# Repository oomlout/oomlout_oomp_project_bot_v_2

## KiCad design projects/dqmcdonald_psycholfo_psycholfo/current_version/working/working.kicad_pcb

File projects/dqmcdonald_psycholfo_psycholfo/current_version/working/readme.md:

# psycholfo
 
## summary 
* id: dqmcdonald_psycholfo_psycholfo
* user: dqmcdonald
* name: psycholfo
* board: psycholfo
* repo: https://github.com/dqmcdonald/PsychoLFO
* src_file_repo_kicad_pcb: PsychoLFO.kicad_pcb
* src_file_repo_kicad_pcb_link: https://github.com/dqmcdonald/PsychoLFO/tree/master/PsychoLFO.kicad_pcb

* src_file_repo_sch: PsychoLFO.sch
* src_file_repo_sch_link: https://github.com/dqmcdonald/PsychoLFO/tree/master/PsychoLFO.sch
* full details link: https://github.com/oomlout/oomlout_oomp_project_bot_v_2/tree/main/projects/dqmcdonald_psycholfo_psycholfo/current_version/working

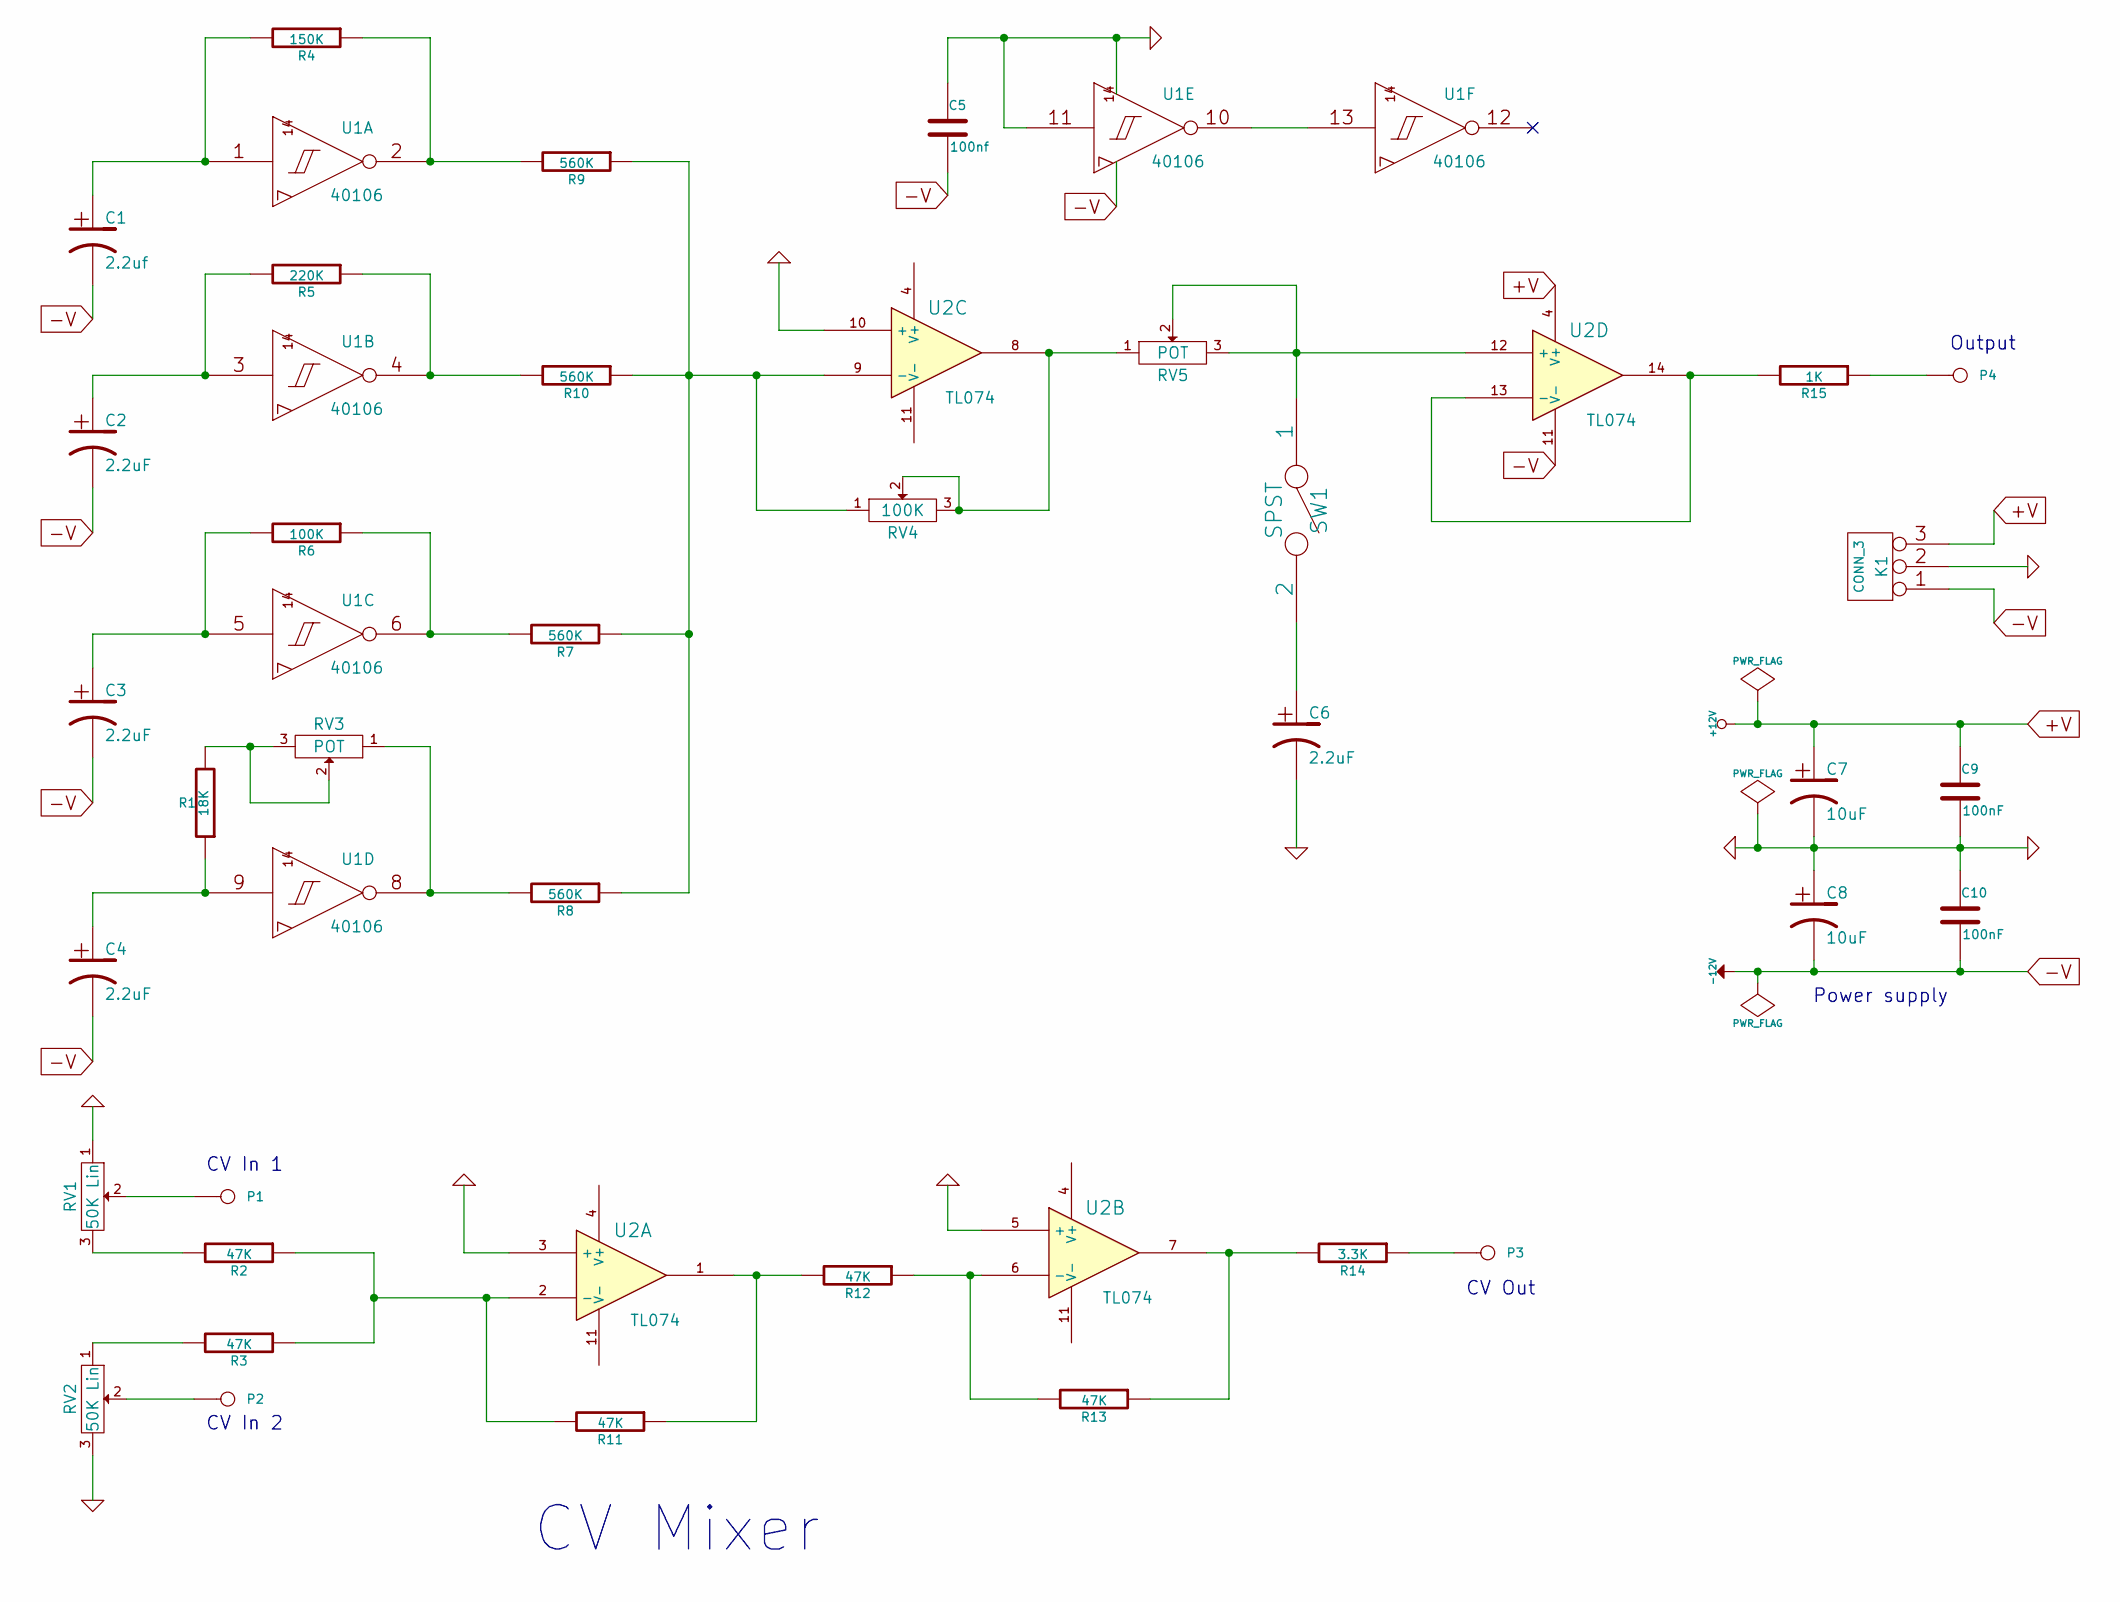
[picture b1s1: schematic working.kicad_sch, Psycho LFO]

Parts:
C1: 2.2uf
C2, C3, C4, C6: 2.2uF
C5: 100nf
C7, C8: 10uF
C9, C10: 100nF
K1: CONN_3
P1, P2, P3: CONN_1
P4: Out
R1: 18K
R2, R3, R11, R12, R13: 47K
R4: 150K
R5: 220K
R6: 100K
R7, R8, R9, R10: 560K
R14: 3.3K
R15: 1K
RV1, RV2: 50K Lin
RV3, RV5: POT
RV4: 100K
SW1: SPST
U1: 40106
U2: TL074

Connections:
+V: C7.1, C9.1, K1.3, U2.4 (V+)
-V: C1.2, C2.2, C3.2, C4.2, C5.2, C8.2, C10.2, K1.1, U1.7 (VSS), U2.11 (V-)
GND: C5.1, C6.2, C7.2, C8.1, C9.2, C10.1, K1.2 (PM), RV1.1, RV2.3, U1.11 (In), U1.14 (VDD), U2.3 (+), U2.5 (+), U2.10 (+)
unnamed: C1.1, R4.2, U1.1 (In)
unnamed: C2.1, R5.2, U1.3 (In)
unnamed: C3.1, R6.2, U1.5 (In)
unnamed: C4.1, R1.1, U1.9 (In)
unnamed: C6.1, SW1.2
unnamed: P1.1, RV1.2
unnamed: P2.1, RV2.2
unnamed: P3.1, R14.1
unnamed: P4.1, R15.1
unnamed: R1.2, RV3.2, RV3.3
unnamed: R2.2, RV1.3
unnamed: R3.2, RV2.1
unnamed: R4.1, R9.2, U1.2 (Out)
unnamed: R6.1, R7.2, U1.6 (Out)
unnamed: R8.2, RV3.1, U1.8 (Out)
unnamed: R7.1, R8.1, R9.1, R10.1, RV4.1, U2.9 (-)
unnamed: R5.1, R10.2, U1.4 (Out)
unnamed: R11.1, R12.2, U2.1
unnamed: R2.1, R3.1, R11.2, U2.2 (-)
unnamed: R12.1, R13.2, U2.6 (-)
unnamed: R13.1, R14.2, U2.7
unnamed: R15.2, U2.13 (-), U2.14
unnamed: RV4.2, RV4.3, RV5.1, U2.8
unnamed: RV5.2, RV5.3, SW1.1, U2.12 (+)
unnamed: U1.10 (Out), U1.13 (In)

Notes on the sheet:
CV Out
Power supply
Output
CV Mixer
CV In 1
CV In 2

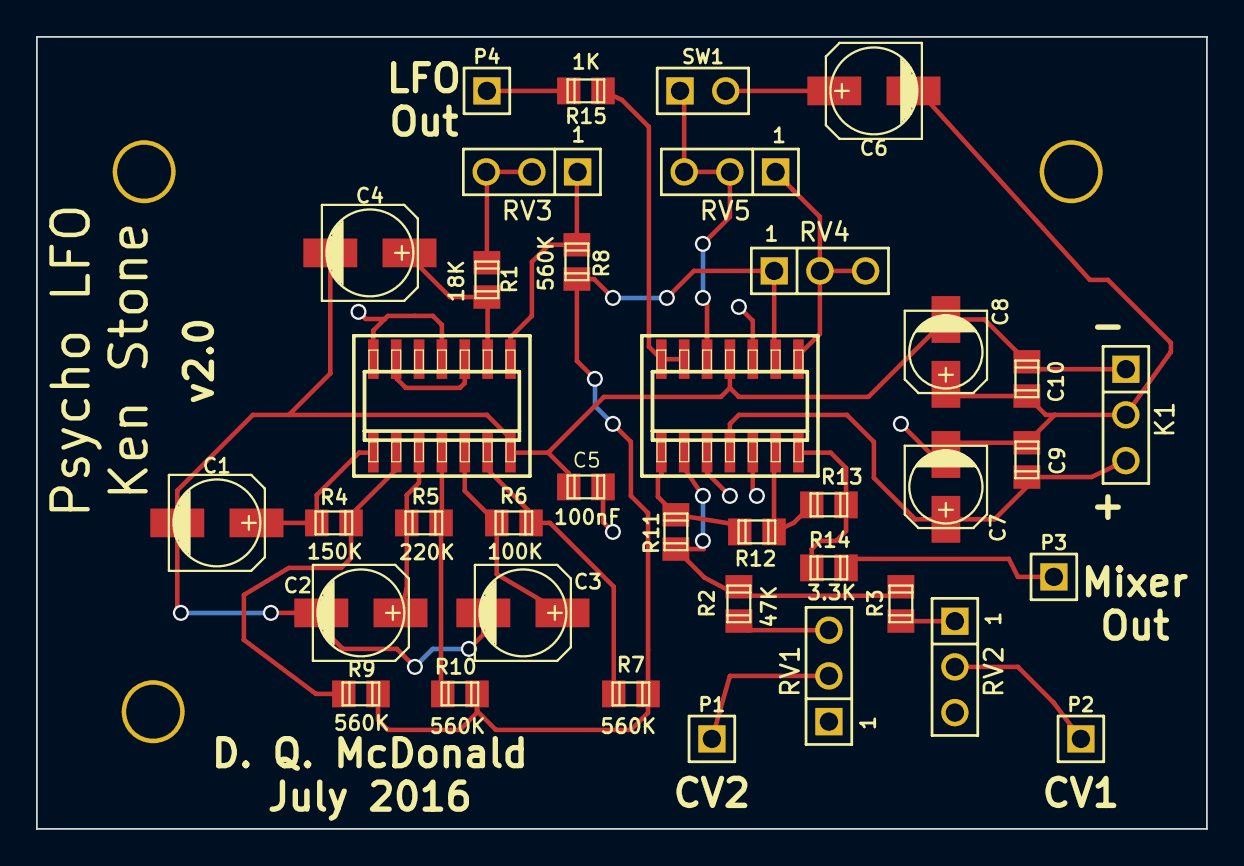
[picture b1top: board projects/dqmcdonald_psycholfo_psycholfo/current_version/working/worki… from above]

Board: 2 copper layers, 65.0 x 44.0 mm, 38 parts (0 on the bottom side), 28 nets.

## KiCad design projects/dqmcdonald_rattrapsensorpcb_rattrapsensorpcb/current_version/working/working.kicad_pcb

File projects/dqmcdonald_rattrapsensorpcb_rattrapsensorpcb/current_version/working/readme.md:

# rattrapsensorpcb
 
## summary 
* id: dqmcdonald_rattrapsensorpcb_rattrapsensorpcb
* user: dqmcdonald
* name: rattrapsensorpcb
* board: rattrapsensorpcb
* repo: https://github.com/dqmcdonald/RatTrapSensorPCB
* src_file_repo_kicad_pcb: RatTrapSensorPCB.kicad_pcb
* src_file_repo_kicad_pcb_link: https://github.com/dqmcdonald/RatTrapSensorPCB/tree/master/RatTrapSensorPCB.kicad_pcb

* src_file_repo_sch: RatTrapSensorPCB.sch
* src_file_repo_sch_link: https://github.com/dqmcdonald/RatTrapSensorPCB/tree/master/RatTrapSensorPCB.sch
* full details link: https://github.com/oomlout/oomlout_oomp_project_bot_v_2/tree/main/projects/dqmcdonald_rattrapsensorpcb_rattrapsensorpcb/current_version/working

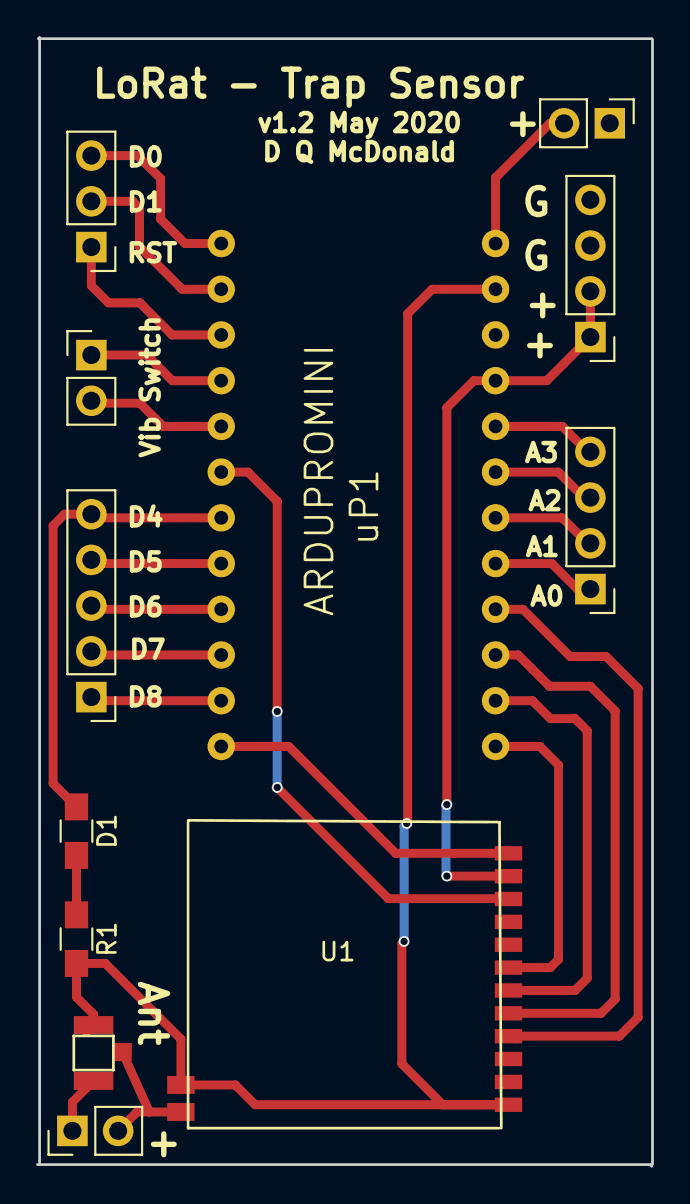
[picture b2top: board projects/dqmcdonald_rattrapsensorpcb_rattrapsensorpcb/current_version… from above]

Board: 2 copper layers, 34.2 x 62.7 mm, 4 parts (0 on the bottom side), 10 nets.

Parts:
D1: LED; R_0805_HandSoldering
R1: 220; R_0805_HandSoldering
U1: LoRaSx1276
uP1: ARDUPROMINI; ArduProMini

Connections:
D3: U1.10, uP1.12
D4: D1.1, uP1.13
D9: U1.12, uP1.18
GND: R1.2, U1.1, U1.14, uP1.10, uP1.20
MISO: U1.5, uP1.28
MOSI: U1.6, uP1.29
NSS: U1.7, uP1.30
unnamed: D1.2, R1.1
SCK: U1.4, uP1.27
V3.3: U1.11, uP1.22

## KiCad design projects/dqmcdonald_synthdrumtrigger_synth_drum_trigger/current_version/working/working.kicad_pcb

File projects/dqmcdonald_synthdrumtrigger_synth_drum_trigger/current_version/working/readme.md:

# synthdrumtrigger
 
## summary 
* id: dqmcdonald_synthdrumtrigger_synth_drum_trigger
* user: dqmcdonald
* name: synthdrumtrigger
* board: synth_drum_trigger
* repo: https://github.com/dqmcdonald/SynthDrumTrigger
* src_file_repo_kicad_pcb: Synth Drum Trigger.kicad_pcb
* src_file_repo_kicad_pcb_link: https://github.com/dqmcdonald/SynthDrumTrigger/tree/master/Synth Drum Trigger.kicad_pcb

* src_file_repo_sch: Synth Drum Trigger.sch
* src_file_repo_sch_link: https://github.com/dqmcdonald/SynthDrumTrigger/tree/master/Synth Drum Trigger.sch
* full details link: https://github.com/oomlout/oomlout_oomp_project_bot_v_2/tree/main/projects/dqmcdonald_synthdrumtrigger_synth_drum_trigger/current_version/working

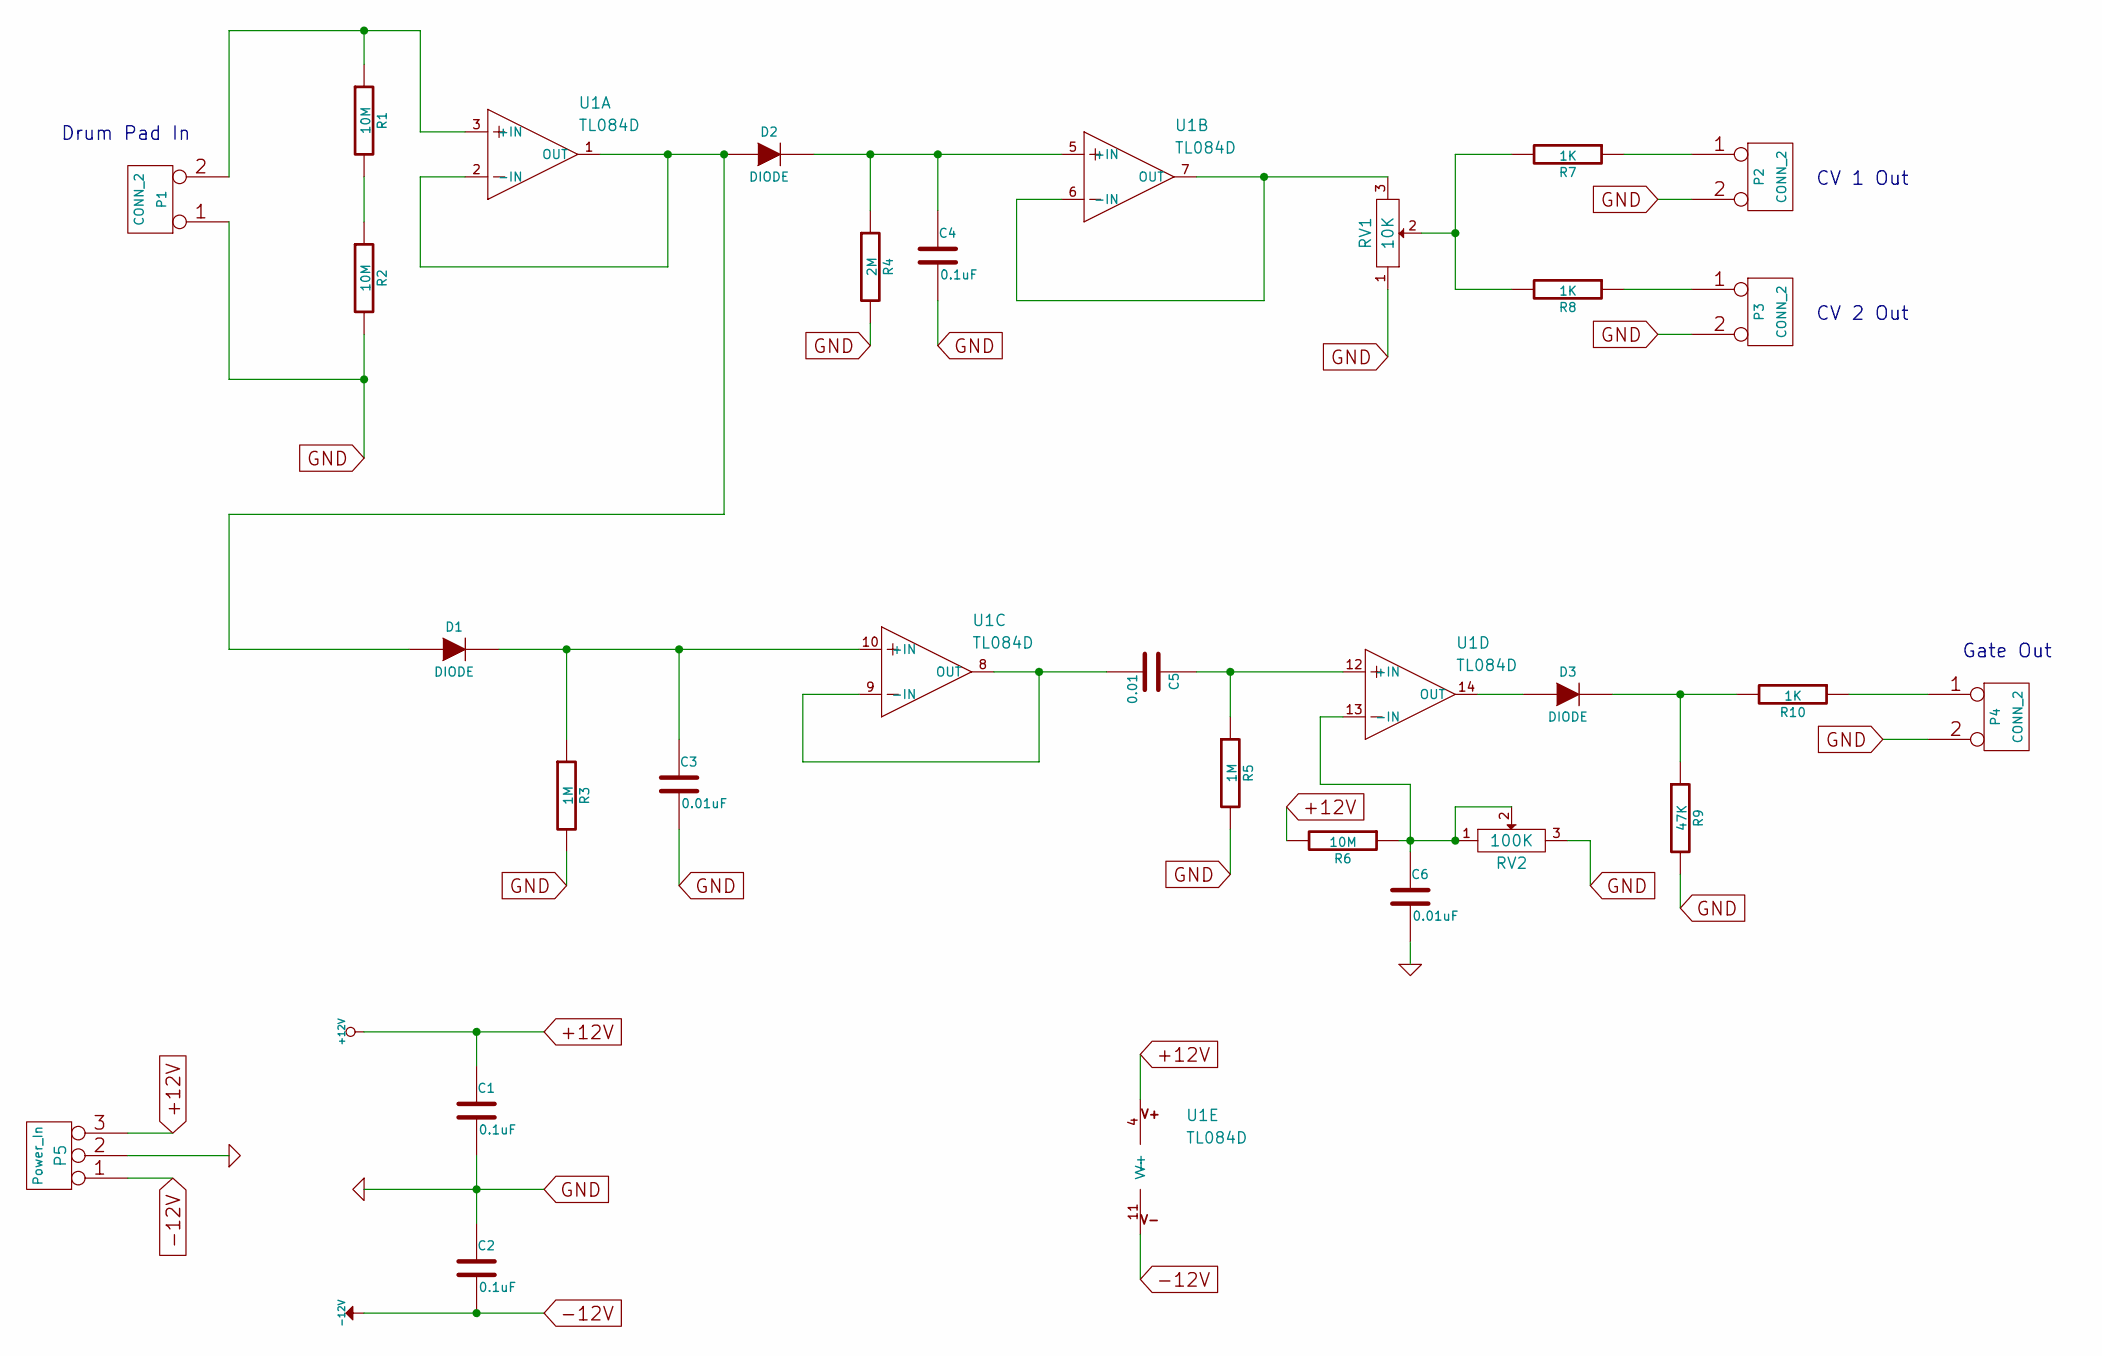
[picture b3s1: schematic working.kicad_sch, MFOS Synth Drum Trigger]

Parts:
C1, C2, C4: 0.1uF
C3, C6: 0.01uF
C5: 0.01
D1, D2, D3: DIODE
P1, P2, P3, P4: CONN_2
P5: Power_In
R1, R2, R6: 10M
R3, R5: 1M
R4: 2M
R7, R8, R10: 1K
R9: 47K
RV1: 10K
RV2: 100K
U1: TL084D; op-amp-SO14

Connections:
+12V: C1.1, P5.3 (+12V), R6.2, U1.4 (V+)
-12V: C2.2, P5.1 (-12V), U1.11 (V-)
GND: C1.2, C2.1, C3.2, C4.2, C6.2, P1.1 (VCC), P2.2 (GND), P3.2 (GND), P4.2 (GND), P5.2 (Gnd), R2.2, R3.2, R4.2, R5.2, R9.2, RV1.1, RV2.3
unnamed: C3.1, D1.2 (K), R3.1, U1.10 (+IN)
unnamed: C4.1, D2.2 (K), R4.1, U1.5 (+IN)
unnamed: C5.1, R5.1, U1.12 (+IN)
unnamed: C5.2, U1.8 (OUT), U1.9 (-IN)
unnamed: C6.1, R6.1, RV2.1, RV2.2, U1.13 (-IN)
unnamed: D1.1 (A), D2.1 (A), U1.1 (OUT), U1.2 (-IN)
unnamed: D3.1 (A), U1.14 (OUT)
unnamed: D3.2 (K), R9.1, R10.2
unnamed: P1.2 (GND), R1.1, U1.3 (+IN)
unnamed: P2.1 (VCC), R7.1
unnamed: P3.1 (VCC), R8.1
unnamed: P4.1 (VCC), R10.1
unnamed: R1.2, R2.1
unnamed: R7.2, R8.2, RV1.2
unnamed: RV1.3, U1.6 (-IN), U1.7 (OUT)

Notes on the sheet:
CV 2 Out
CV 1 Out
Gate Out
Drum Pad In

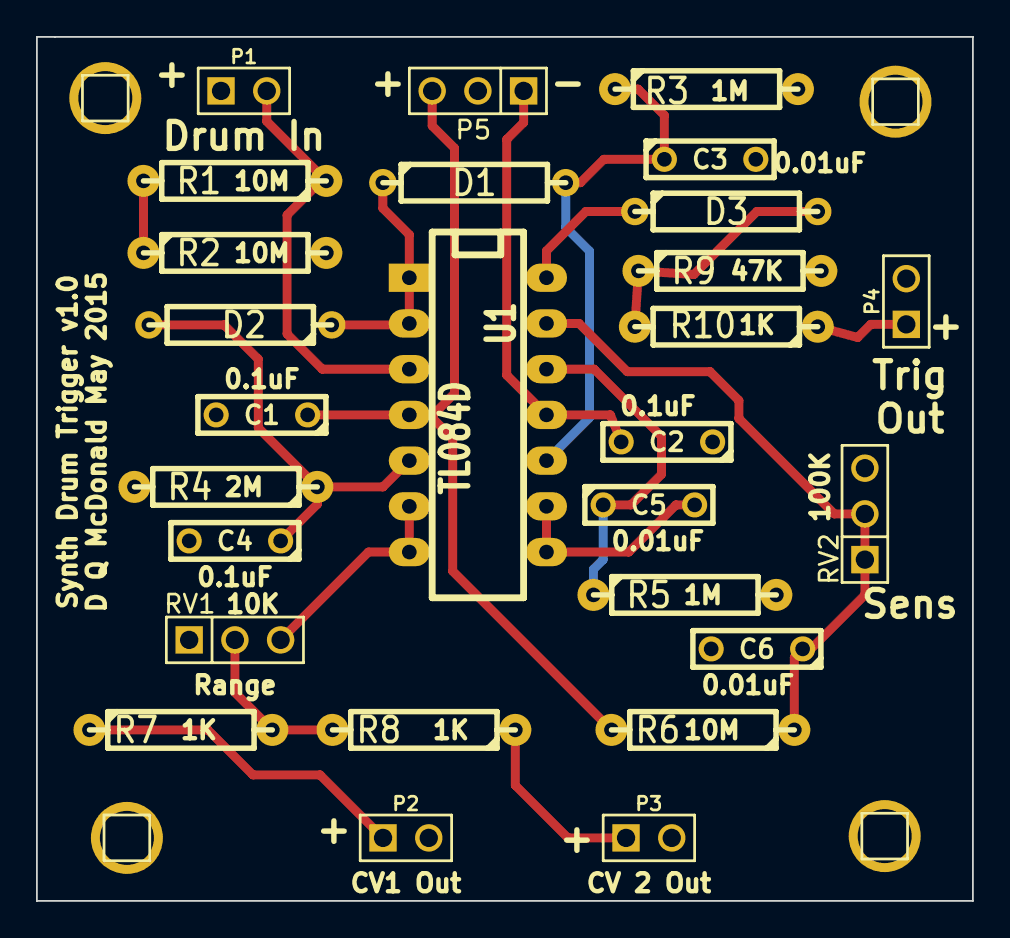
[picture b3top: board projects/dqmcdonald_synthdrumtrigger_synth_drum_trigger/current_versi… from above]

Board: 2 copper layers, 52.0 x 48.0 mm, 27 parts (0 on the bottom side), 18 nets.

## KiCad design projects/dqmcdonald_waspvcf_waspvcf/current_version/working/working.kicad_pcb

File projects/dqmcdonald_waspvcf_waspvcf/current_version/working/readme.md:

# waspvcf
 
## summary 
* id: dqmcdonald_waspvcf_waspvcf
* user: dqmcdonald
* name: waspvcf
* board: waspvcf
* repo: https://github.com/dqmcdonald/WaspVCF
* src_file_repo_kicad_pcb: WaspVCF.kicad_pcb
* src_file_repo_kicad_pcb_link: https://github.com/dqmcdonald/WaspVCF/tree/master/WaspVCF.kicad_pcb

* src_file_repo_sch: WaspVCF.sch
* src_file_repo_sch_link: https://github.com/dqmcdonald/WaspVCF/tree/master/WaspVCF.sch
* full details link: https://github.com/oomlout/oomlout_oomp_project_bot_v_2/tree/main/projects/dqmcdonald_waspvcf_waspvcf/current_version/working

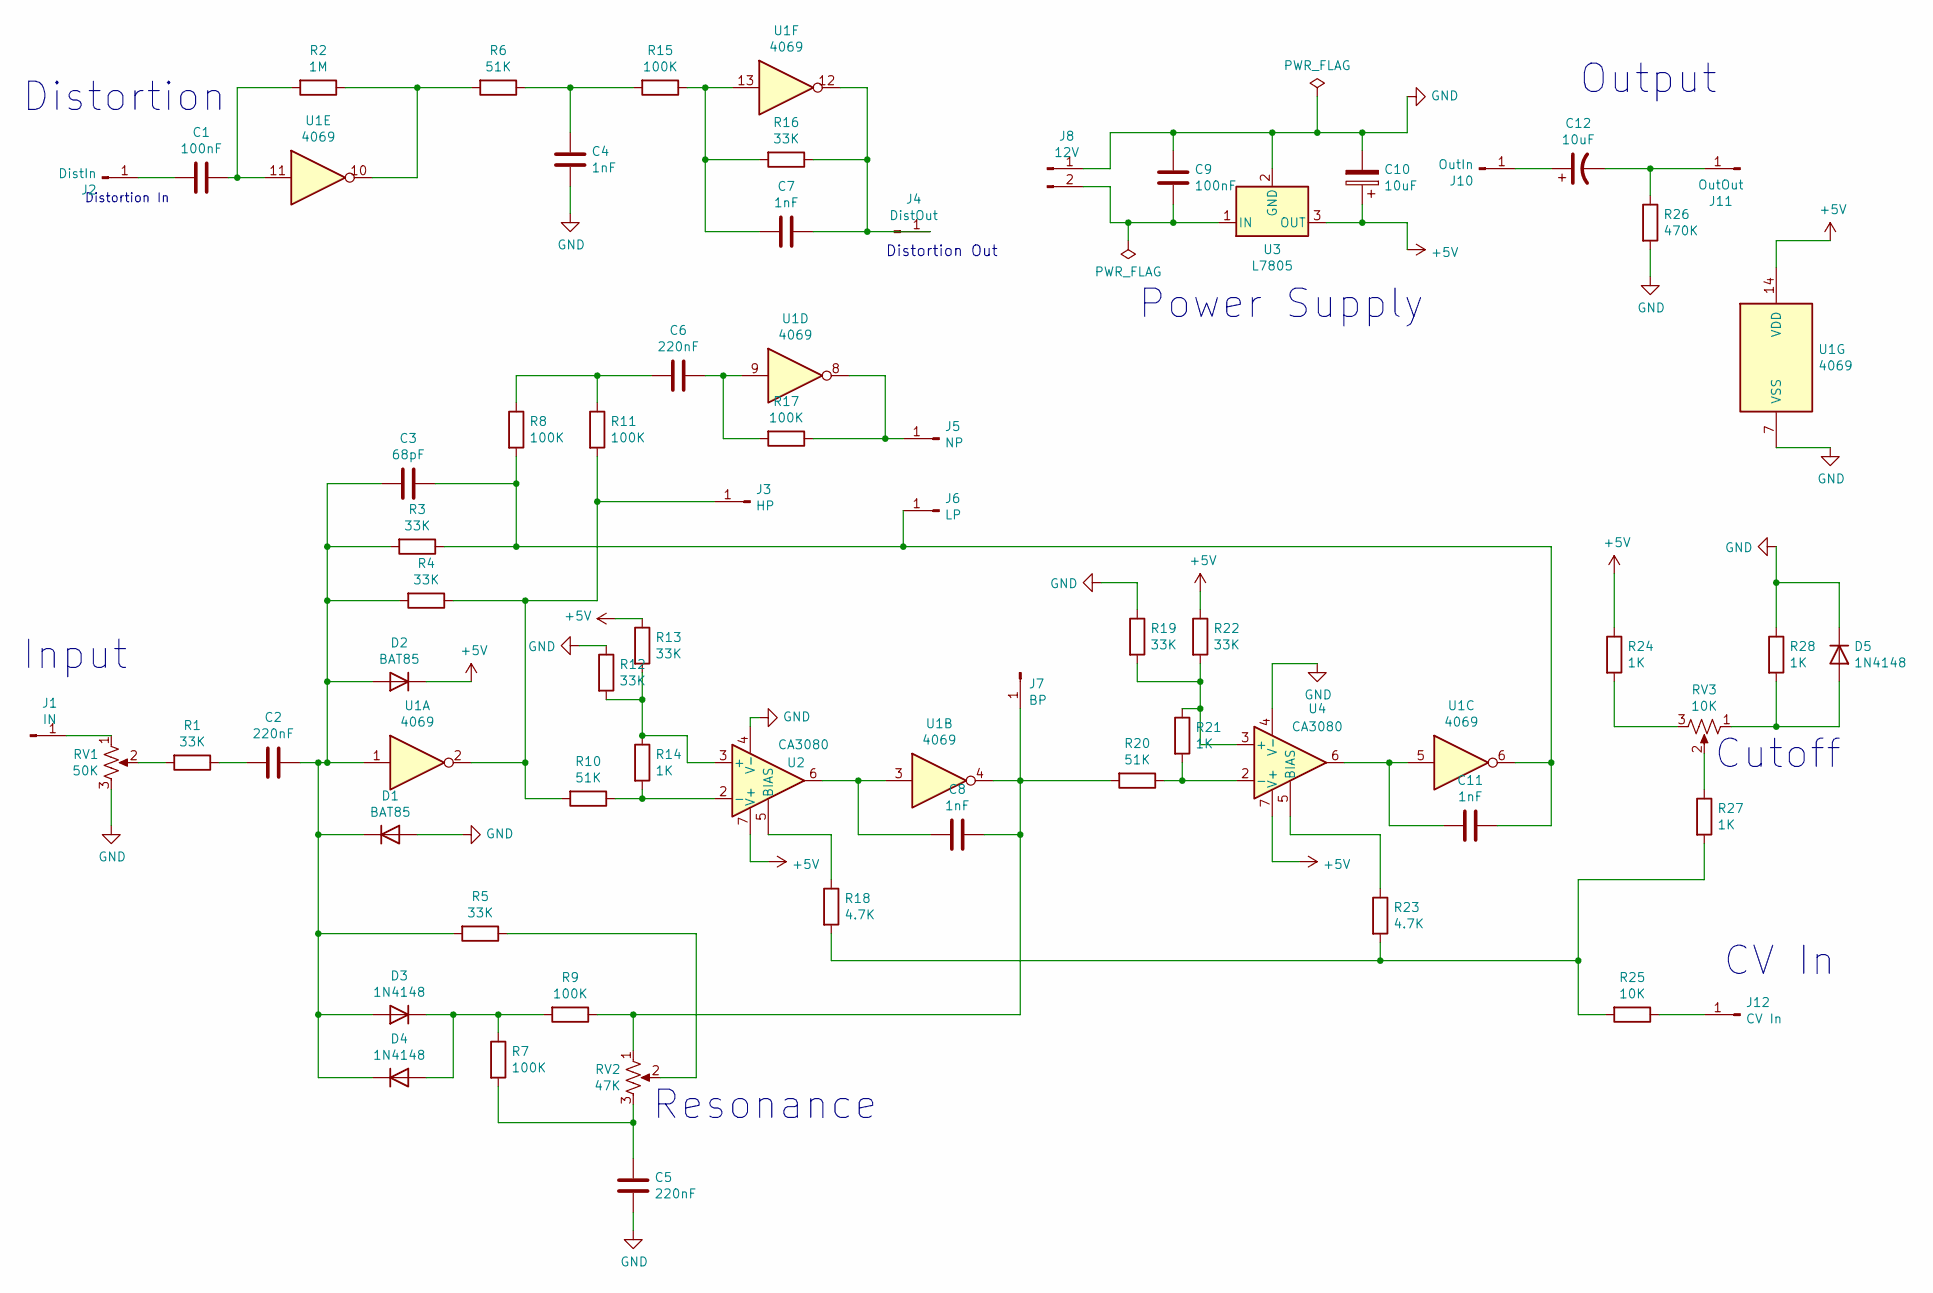
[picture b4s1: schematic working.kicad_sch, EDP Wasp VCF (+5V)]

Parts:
C1, C9: 100nF; C_Disc_D6.0mm_W2.5mm_P5.00mm
C2, C5, C6: 220nF; C_Disc_D6.0mm_W2.5mm_P5.00mm
C3: 68pF; C_Disc_D6.0mm_W2.5mm_P5.00mm
C4, C7, C8, C11: 1nF; C_Disc_D6.0mm_W2.5mm_P5.00mm
C10, C12: 10uF; CP_Radial_D5.0mm_P2.50mm
D1, D2: BAT85; D_T-1_P5.08mm_Horizontal
D3, D4, D5: 1N4148; D_T-1_P5.08mm_Horizontal
J1: IN; Pin_Header_Straight_1x01_Pitch2.54mm
J2: DistIn; Pin_Header_Straight_1x01_Pitch2.54mm
J3: HP; Pin_Header_Straight_1x01_Pitch2.54mm
J4: DistOut; Pin_Header_Straight_1x01_Pitch2.54mm
J5: NP; Pin_Header_Straight_1x01_Pitch2.54mm
J6: LP; Pin_Header_Straight_1x01_Pitch2.54mm
J7: BP; Pin_Header_Straight_1x01_Pitch2.54mm
J8: 12V; Pin_Header_Straight_1x02_Pitch2.54mm
J10: OutIn; Pin_Header_Straight_1x01_Pitch2.54mm
J11: OutOut; Pin_Header_Straight_1x01_Pitch2.54mm
J12: CV In; Pin_Header_Straight_1x01_Pitch2.54mm
R1, R3, R4, R5, R12, R13, R16, R19, R22: 33K; R_Axial_DIN0207_L6.3mm_D2.5mm_P7.62mm_Horizontal
R2: 1M; R_Axial_DIN0207_L6.3mm_D2.5mm_P7.62mm_Horizontal
R6, R10, R20: 51K; R_Axial_DIN0207_L6.3mm_D2.5mm_P7.62mm_Horizontal
R7, R8, R9, R11, R15, R17: 100K; R_Axial_DIN0207_L6.3mm_D2.5mm_P7.62mm_Horizontal
R14, R21, R24, R27, R28: 1K; R_Axial_DIN0207_L6.3mm_D2.5mm_P7.62mm_Horizontal
R18, R23: 4.7K; R_Axial_DIN0207_L6.3mm_D2.5mm_P7.62mm_Horizontal
R25: 10K; R_Axial_DIN0207_L6.3mm_D2.5mm_P7.62mm_Horizontal
R26: 470K; R_Axial_DIN0207_L6.3mm_D2.5mm_P7.62mm_Horizontal
RV1: 50K; Pin_Header_Straight_1x03_Pitch2.54mm
RV2: 47K; Pin_Header_Straight_1x03_Pitch2.54mm
RV3: 10K; Pin_Header_Straight_1x03_Pitch2.54mm
U1: 4069; DIP-14_W7.62mm_Socket_LongPads
U2: CA3080; DIP-8_W7.62mm_Socket_LongPads
U3: L7805; TO-220-3_Vertical
U4: CA3080; DIP-8_W7.62mm_LongPads

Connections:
+5V: C10.1, D2.1 (K), R13.1, R22.1, R24.1, U1.14 (VDD), U2.7 (V+), U3.3 (OUT), U4.7 (V+)
GND: C4.2, C5.2, C9.1, C10.2, D1.2 (A), D5.1 (K), J8.1, R12.1, R19.1, R26.2, R28.1, RV1.3, U1.7 (VSS), U2.4 (V-), U3.2 (GND), U4.4 (V-)
unnamed: C1.1, R2.2, U1.11
unnamed: C1.2, J2.1
unnamed: C2.1, C3.2, D1.1 (K), D2.2 (A), D3.2 (A), D4.1 (K), R3.2, R4.2, R5.2, U1.1
unnamed: C2.2, R1.1
unnamed: C4.1, R6.1, R15.2
unnamed: C5.1, R7.2, RV2.3
unnamed: C6.1, R17.2, U1.9
unnamed: C6.2, R8.1, R11.1
unnamed: C7.1, J4.1, R16.1, U1.12
unnamed: C7.2, R15.1, R16.2, U1.13
unnamed: C8.1, J7.1, R9.1, R20.2, RV2.1, U1.4
unnamed: C8.2, U1.3, U2.6
unnamed: C9.2, J8.2, U3.1 (IN)
unnamed: C3.1, C11.1, J6.1, R3.1, R8.2, U1.6
unnamed: C11.2, U1.5, U4.6
unnamed: C12.1, J10.1
unnamed: C12.2, J11.1, R26.1
unnamed: D3.1 (K), D4.2 (A), R7.1, R9.2
unnamed: D5.2 (A), R28.2, RV3.1
unnamed: J1.1, RV1.1
unnamed: J3.1, R4.1, R10.2, R11.2, U1.2
unnamed: J5.1, R17.1, U1.8
unnamed: J12.1, R25.1
unnamed: R1.2, RV1.2
unnamed: R2.1, R6.2, U1.10
unnamed: R5.1, RV2.2
unnamed: R10.1, R14.2, U2.2 (-)
unnamed: R12.2, R13.2, R14.1, U2.3 (+)
unnamed: R18.1, U2.5 (BIAS)
unnamed: R18.2, R23.2, R25.2, R27.2
unnamed: R19.2, R21.1, R22.2, U4.3 (+)
unnamed: R20.1, R21.2, U4.2 (-)
unnamed: R23.1, U4.5 (BIAS)
unnamed: R24.2, RV3.3
unnamed: R27.1, RV3.2

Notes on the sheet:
Input
Distortion In
CV In
Distortion Out
Distortion
Cutoff
Resonance
Power Supply
Output

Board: 2 copper layers, 63 parts (0 on the bottom side), 37 nets, no tracks yet.

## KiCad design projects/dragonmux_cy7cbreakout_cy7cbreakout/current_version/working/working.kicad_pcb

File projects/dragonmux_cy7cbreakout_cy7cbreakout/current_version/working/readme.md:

# cy7cbreakout
 
## summary 
* id: dragonmux_cy7cbreakout_cy7cbreakout
* user: dragonmux
* name: cy7cbreakout
* board: cy7cbreakout
* repo: https://github.com/dragonmux/CY7CBreakout
* src_file_repo_kicad_pcb: CY7CBreakout.kicad_pcb
* src_file_repo_kicad_pcb_link: https://github.com/dragonmux/CY7CBreakout/tree/main/CY7CBreakout.kicad_pcb

* src_file_repo_sch: 
* src_file_repo_sch_link: https://github.com/dragonmux/CY7CBreakout/tree/main/
* full details link: https://github.com/oomlout/oomlout_oomp_project_bot_v_2/tree/main/projects/dragonmux_cy7cbreakout_cy7cbreakout/current_version/working

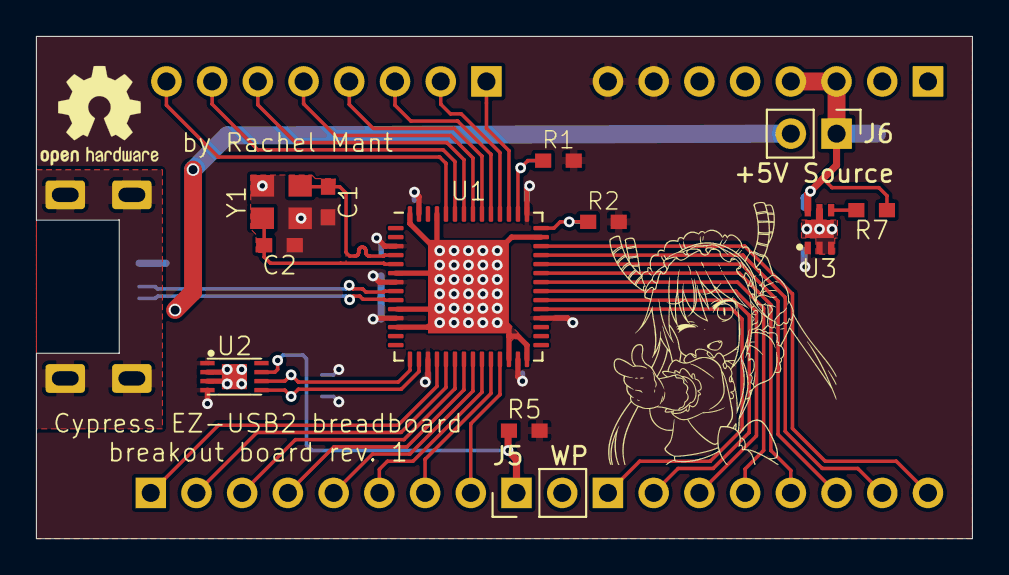
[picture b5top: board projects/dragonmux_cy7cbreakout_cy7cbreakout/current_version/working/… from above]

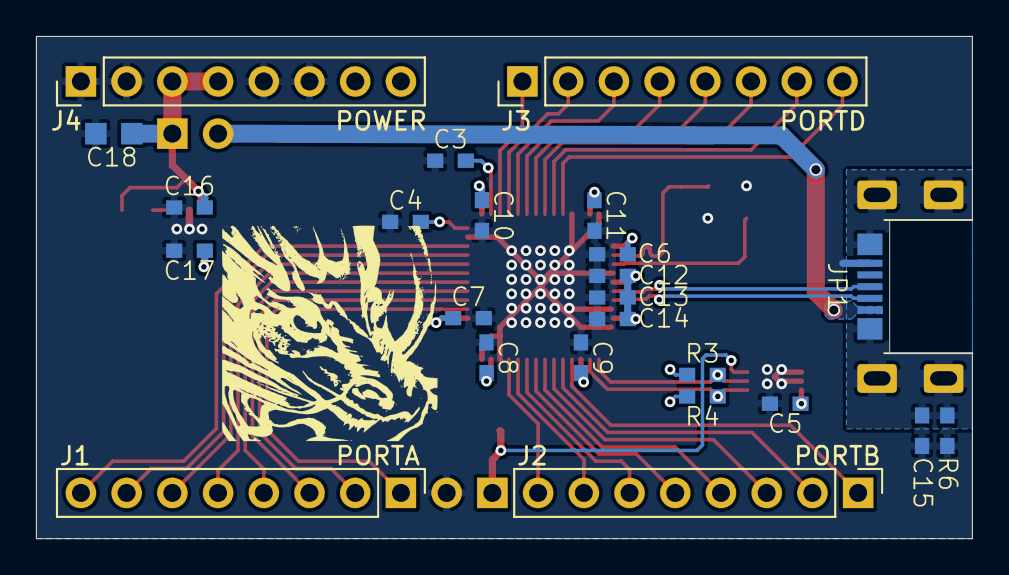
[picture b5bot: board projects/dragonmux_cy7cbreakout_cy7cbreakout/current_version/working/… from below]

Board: 2 copper layers, 52.0 x 27.9 mm, 39 parts (25 on the bottom side), 39 nets.

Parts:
C1, C2: 15pF; C0603
C3, C4: 10uF; C0603
C5, C6, C7, C8, C9, C10, C11, C15: 0.1uF; C0603
C12: 0.22uF; C0603
C13: 10nF; C0603
C14: 1nF; C0603
C16, C17: 4.7uF; C0603
C18: 47uF; C0805
DRG1: トール; トール-12.9x14.8
DRG2: Nagadreth; Nagadreth-12.0x12.0
J1: PORTA; PinHeader_1x08_P2.54mm_Vertical
J2: PORTB; PinHeader_1x08_P2.54mm_Vertical
J3: PORTD; PinHeader_1x08_P2.54mm_Vertical
J4: POWER; PinHeader_1x08_P2.54mm_Vertical
J5: WP; PinHeader_1x02_P2.54mm_Vertical
J6: +5V Source; PinHeader_1x02_P2.54mm_Vertical
JP1: USB-Micro-B; MICRO-USB-B-(IN_PCB)
LOGO1: Logo_Open_Hardware_Small; OSHW-Logo2_7.3x6mm_SilkScreen
R1, R7: 100k; R0603
R2, R5: 10k; R0603
R3, R4: 2k2; R0603
R6: 1M; R0603
U1: CY7C68013A-56LTX; QFN-56-1EP_8x8mm_P0.5mm_EP4.5x5.2mm
U2: M24128; UFDFPN8
U3: TLV755P; DFN6-2x2mm
Y1: 24MHz; SMD2520

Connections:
+3V3: C5.1, C6.1, C7.1, C8.1, C9.1, C10.1, C11.1, C12.1, C13.1, C14.1, C17.1, J4.7, J4.8, R1.1, R2.1, R3.1, R4.1, R5.2, U1.3, U1.7, U1.11, U1.17, U1.27, U1.32, U1.43, U1.55, U2.1, U2.4, U3.1
+5V: C16.2, C18.1, J4.3, J4.4, J6.1, R7.2, U3.6
/Breadboard Connectors/PA0: J1.1, U1.33
/Breadboard Connectors/PA1: J1.2, U1.34
/Breadboard Connectors/PA2: J1.3, U1.35
/Breadboard Connectors/PA3: J1.4, U1.36
/Breadboard Connectors/PA4: J1.5, U1.37
/Breadboard Connectors/PA5: J1.6, U1.38
/Breadboard Connectors/PA6: J1.7, U1.39
/Breadboard Connectors/PA7: J1.8, U1.40
/Breadboard Connectors/PB0: J2.1, U1.18
/Breadboard Connectors/PB1: J2.2, U1.19
/Breadboard Connectors/PB2: J2.3, U1.20
/Breadboard Connectors/PB3: J2.4, U1.21
/Breadboard Connectors/PB4: J2.5, U1.22
/Breadboard Connectors/PB5: J2.6, U1.23
/Breadboard Connectors/PB6: J2.7, U1.24
/Breadboard Connectors/PB7: J2.8, U1.25
/Breadboard Connectors/PD0: J3.1, U1.45
/Breadboard Connectors/PD1: J3.2, U1.46
/Breadboard Connectors/PD2: J3.3, U1.47
/Breadboard Connectors/PD3: J3.4, U1.48
/Breadboard Connectors/PD4: J3.5, U1.49
/Breadboard Connectors/PD5: J3.6, U1.50
/Breadboard Connectors/PD6: J3.7, U1.51
/Breadboard Connectors/PD7: J3.8, U1.52
/Processor+USB/D+: JP1.D+, U1.8
/Processor+USB/D-: JP1.D-, U1.9
/Processor+USB/OSC+: C1.1, U1.4, Y1.1
/Processor+USB/OSC-: C2.1, U1.5, Y1.3
/Processor+USB/SCL: R3.2, U1.15, U2.6
/Processor+USB/SDA: R4.2, U1.16, U2.5
/Processor+USB/VBUS: J6.2, JP1.VCC
/Processor+USB/WAKEUP: C3.1, R1.2, U1.44
/Processor+USB/~RESET: C4.1, R2.2, U1.42
/Supply + Support Elements/EEPROM_WC: J5.1, R5.1, U2.7
Earth: C15.1, JP1.SHIELD, R6.2
GND: C1.2, C2.2, C3.2, C4.2, C5.2, C6.2, C7.2, C8.2, C9.2, C10.2, C11.2, C12.2, C13.2, C14.2, C15.2, C16.1, C17.2, C18.2, J4.1, J4.2, J4.5, J4.6, J5.2, JP1.GND1, R6.1, U1.6, U1.10, U1.12, U1.26, U1.28, U1.41, U1.53, U1.56, U1.57, U2.2, U2.3, U2.GND, U3.2, U3.3, U3.5, U3.GND, Y1.2, Y1.4
unnamed: R7.1, U3.4

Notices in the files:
projects/dragonmux_headphoneamp_audiointerface/current_version/working/working.kicad_pcb:
CERN OHL
